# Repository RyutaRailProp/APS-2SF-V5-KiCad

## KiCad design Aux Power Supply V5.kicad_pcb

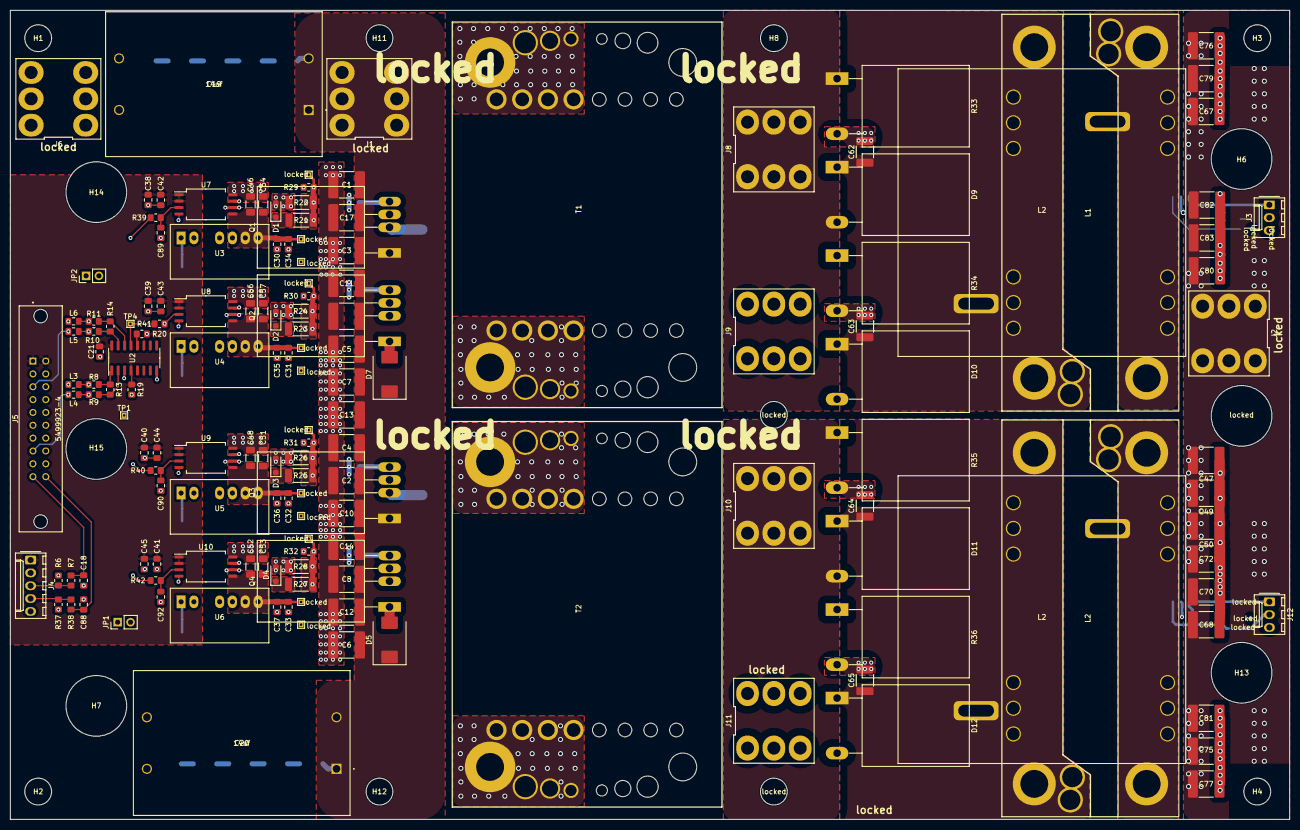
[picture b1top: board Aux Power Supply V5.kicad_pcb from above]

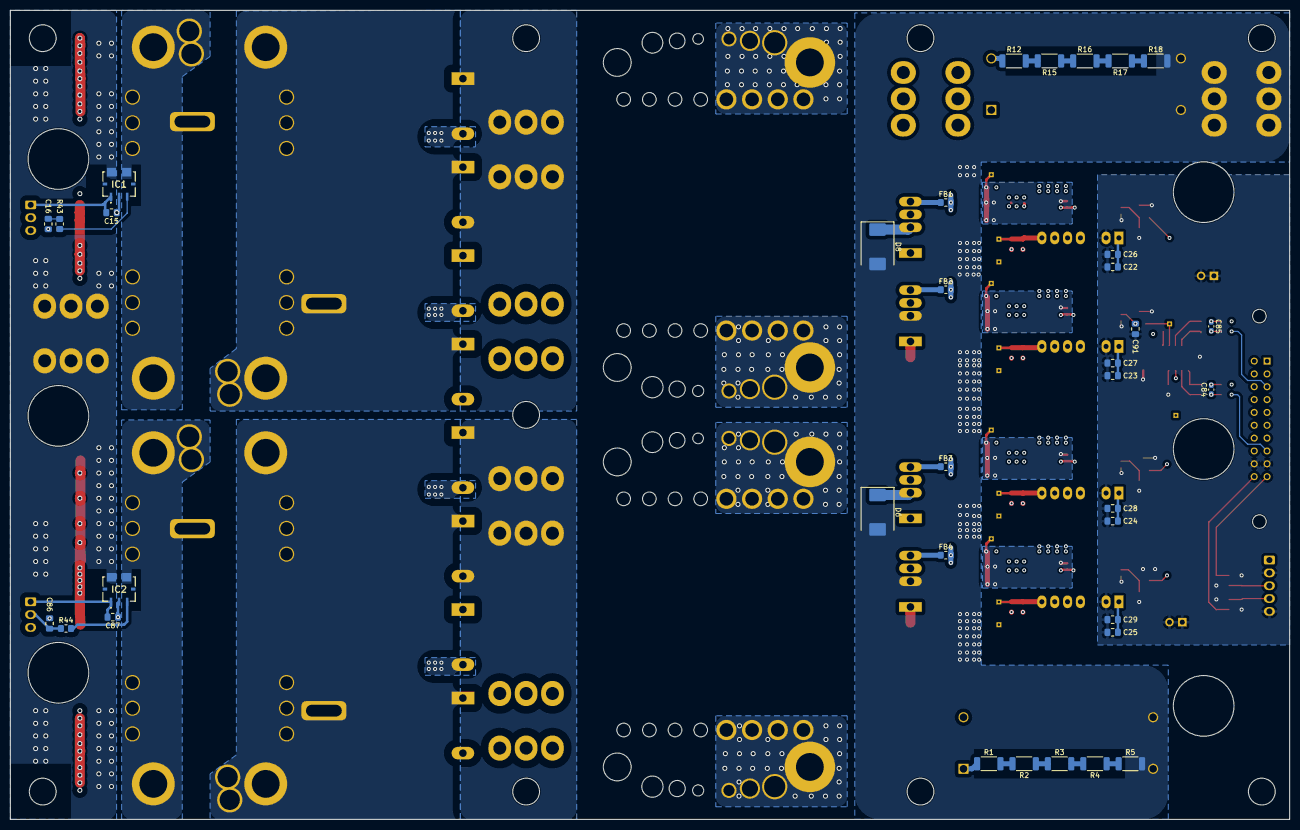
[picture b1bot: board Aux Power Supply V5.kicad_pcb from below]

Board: 4 copper layers, 253.0 x 160.0 mm, 208 parts (35 on the bottom side), 78 nets.

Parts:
C1, C2, C3, C4, C5, C6, C7, C8, C9, C10, C11, C12, C13, C14, C17: C; C_2220_5650Metric_Pad1.97x5.40mm_HandSolder
C15, C16, C21, C26, C27, C28, C29, C42, C43, C44, C45, C86, C87: 0.1uf; C_0805_2012Metric_Pad1.18x1.45mm_HandSolder
C18, C88: 3.9uf; C_0805_2012Metric_Pad1.18x1.45mm_HandSolder
C19, C20: 14uf; Film Cap, C4AxxBWxxxxx3J, 28 x 42 x 37
C22, C23, C24, C25, C34, C35, C36, C37: 4.7uf; C_0805_2012Metric_Pad1.18x1.45mm_HandSolder
C30, C31, C32, C33, C38, C39, C40, C41: 1uf; C_0805_2012Metric_Pad1.18x1.45mm_HandSolder
C46, C48, C51, C52, C53, C54, C56, C57: 0.1uf; C_1206_3216Metric_Pad1.33x1.80mm_HandSolder
C47, C49, C50, C67, C68, C70, C72, C75, C76, C77, C79, C80, C81, C82, C83: 22201C106KAT2A; C_2220_5650Metric_Pad1.97x5.40mm_HandSolder
C62, C63, C64, C65: 18121A472JAT2A; C_1812_4532Metric_Pad1.57x3.40mm_HandSolder
C84, C85: 56pF; C_0603_1608Metric_Pad1.08x0.95mm_HandSolder
C89, C90, C91, C92: 10uf; C_0805_2012Metric_Pad1.18x1.45mm_HandSolder
D1, D2, D3, D4: D_Small; D_SOD-123F
D5, D6, D7, D8: STTH212S; D_SMC
D9, D10, D11, D12: APT30S20BG; TO-247-2_Horizontal_TabDown_NoHole
FB1, FB2, FB3, FB4: 180ohm 100MHZ; R_0805_2012Metric_Pad1.20x1.40mm_HandSolder
H1, H2, H3, H4, H8, H11, H12: MountingHole; MountingHole_5.3mm_M5_DIN965
H6, H7, H13, H14, H15: MountingHole; MountingHole_12mm_M5_SpringClamp
IC1, IC2: ACS780LLRTR-050U-T; ACS780LLRTR050BT
J1, J2, J6, J8, J9, J10, J11: Screw_Terminal_01x01; 7808 Keystone M5 Terminal
J3, J12: I_Sense_R; Molex_KK-254_AE-6410-03A_1x03_P2.54mm_Vertical
J4: Conn_01x05; Molex_KK-254_AE-6410-05A_1x05_P2.54mm_Vertical
J5: 5499923-4; TE_5499923-4
JP1, JP2: Jumper; PinHeader_1x02_P2.54mm_Vertical
L1, L2#3: 26uH; ETD49 Core MB
L2, L2#2: 26uH; CWS-1HW-12203
L3, L4, L5, L6: 1uH; L_0805_2012Metric_Pad1.15x1.40mm_HandSolder
Q1, Q2, Q3, Q4: UJ4C075018K4S; TO-247-4_Horizontal_TabDown_NoHole
R1, R2, R3, R4, R5, R12, R15, R16, R17, R18: 100k; R_2010_5025Metric
R6, R13, R14, R19, R20, R29, R30, R31, R32, R37, R39, R40, R41, R42: 10k; R_0805_2012Metric_Pad1.20x1.40mm_HandSolder
R7, R38, R43, R44: 100R; R_0805_2012Metric_Pad1.20x1.40mm_HandSolder
R8, R9, R10, R11: 5k; R_0805_2012Metric_Pad1.20x1.40mm_HandSolder
R21, R23, R25, R27: 1; R_2010_5025Metric_Pad1.40x2.65mm_HandSolder
R22, R24, R26, R28: 5; R_2010_5025Metric_Pad1.40x2.65mm_HandSolder
R33, R34, R35, R36: R; TO-247-2_Horizontal_TabDown_NoHole
T1, T2: Transformer_1P_1S; E65 Core Main Board
TP1, TP4: IN+; TestPoint_THTPad_1.0x1.0mm_Drill0.5mm
TP5, TP6, TP7, TP8: +15H1; TestPoint_THTPad_1.0x1.0mm_Drill0.5mm
TP9, TP10, TP11, TP12: -5H1; TestPoint_THTPad_1.0x1.0mm_Drill0.5mm
TP13, TP14, TP15, TP16: PWM; TestPoint_THTPad_1.0x1.0mm_Drill0.5mm
U2: AM26LS33; SOIC-16_3.9x9.9mm_P1.27mm
U3, U4, U5, U6: AM2D-2418SZ; SIP-7 (pins 1, 2, 4,5, 6, 7)
U7, U8, U9, U10: STGAP2SICSC; SOIC-8_7.5x5.85mm_P1.27mm
locked: MountingHole; MountingHole_12mm_M5_SpringClamp
locked#2, locked#3: MountingHole; MountingHole_5.3mm_M5_DIN965

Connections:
1_HI: J5.5, L5.1
1_LO: J5.6, L6.1
2_HI: J5.16, L3.1
2_LO: J5.15, L4.1
+5V: C15.2, C21.1, C38.1, C39.1, C40.1, C41.1, C42.1, C43.1, C44.1, C45.1, C87.2, IC1.1 (VCC), IC2.1 (VCC), J3.1, J4.1, J5.1, J5.2, J12.1, R19.1, R20.2, U2.4 (EN), U2.16 (VDD), U7.1 (VCC), U7.2 (IN+), U8.1 (VCC), U8.2 (IN+), U9.1 (VCC), U9.2 (IN+), U10.1 (VCC), U10.2 (IN+)
+18V_BOT_T1: C31.1, C35.1, C56.1, C57.1, TP6.1, U4.7 (VOUT+), U8.5 (VCC2)
+18V_BOT_T2: C33.1, C37.1, C52.1, C53.1, TP8.1, U6.7 (VOUT+), U10.5 (VCC2)
+18V_TOP_T1: C30.1, C34.1, C46.1, C54.1, TP5.1, U3.7 (VOUT+), U7.5 (VCC2)
+18V_TOP_T2: C32.1, C36.1, C48.1, C51.1, TP7.1, U5.7 (VOUT+), U9.5 (VCC2)
+24V: C22.1, C23.1, C24.1, C25.1, C26.1, C27.1, C28.1, C29.1, J5.7, J5.8, U3.1 (VIN+), U4.1 (VIN+), U5.1 (VIN+), U6.1 (VIN+)
+72V_1: IC1.5 (IP+), L1.2, L2#2.2
+72V_2: IC2.5 (IP+), L2.2, L2#3.2
+72V_OUT: C47.2, C49.2, C50.2, C67.2, C68.2, C70.2, C72.2, C75.2, C76.2, C77.2, C79.2, C80.2, C81.2, C82.2, C83.2, IC1.6 (IP-), IC2.6 (IP-), J2.1
CLAMP_BOT_T1: FB2.2, R23.1, R24.1, R30.2, TP14.1, U8.7 (CLAMP)
CLAMP_BOT_T2: FB4.2, R27.1, R28.1, R32.2, TP16.1, U10.7 (CLAMP)
CLAMP_TOP_T1: FB1.2, R21.1, R22.1, R29.2, TP13.1, U7.7 (CLAMP)
CLAMP_TOP_T2: FB3.2, R25.1, R26.1, R31.2, TP15.1, U9.7 (CLAMP)
Ch1: R39.2, R41.2, TP4.1, U2.13 (Out4)
Ch2: R40.2, R42.2, TP1.1, U2.3 (Out1)
DC_IN: C1.1, C2.1, C3.1, C4.1, C5.1, C6.1, C7.1, C8.1, C9.1, C10.1, C11.1, C12.1, C13.1, C14.1, C17.1, C19.1, C20.1, D5.1 (K), D7.1 (K), J1.1, Q1.1 (D), Q3.1 (D), R1.1, R12.1
GATE_BOT_T1: D2.2 (A), R24.2, U8.6 (OUT)
GATE_BOT_T2: D4.2 (A), R28.2, U10.6 (OUT)
GATE_TOP_T1: D1.2 (A), R22.2, U7.6 (OUT)
GATE_TOP_T2: D3.2 (A), R26.2, U9.6 (OUT)
GND: C15.1, C16.2, C18.2, C21.2, C22.2, C23.2, C24.2, C25.2, C26.2, C27.2, C28.2, C29.2, C38.2, C39.2, C40.2, C41.2, C42.2, C43.2, C44.2, C45.2, C86.2, C87.1, C88.2, C89.1, C90.1, C91.1, C92.1, IC1.2 (GND), IC2.2 (GND), J3.3, J4.2, J4.5, J5.17, J5.18, J12.3, JP1.1, JP1.2, JP2.1, JP2.2, R6.1, R19.2, R37.1, U2.8 (GND), U3.2 (VIN-), U4.2 (VIN-), U5.2 (VIN-), U6.2 (VIN-), U7.4 (GND1), U8.4 (GND1), U9.4 (GND1), U10.4 (GND1)
GNDPWR: C1.2, C2.2, C3.2, C4.2, C5.2, C6.2, C7.2, C8.2, C9.2, C10.2, C11.2, C12.2, C13.2, C14.2, C17.2, C19.2, C20.2, D6.2 (A), D8.2 (A), J6.1, Q2.2 (S), Q4.2 (S), R5.2, R18.2
H1: R10.1, R14.2, U2.15 (B4)
H2: R8.1, R13.2, U2.1 (B1)
I_Sense_1: C18.1, J5.19, R7.2
I_Sense_2: C88.1, J5.20, R38.2
KELV_BOT_T1: C31.2, C35.2, C56.2, C57.2, Q2.3 (DS), R30.1, TP10.1, U4.5 (VOUT-), U8.8 (VEE)
KELV_BOT_T2: C33.2, C37.2, C52.2, C53.2, Q4.3 (DS), R32.1, TP12.1, U6.5 (VOUT-), U10.8 (VEE)
KELV_TOP_T1: C30.2, C34.2, C46.2, C54.2, Q1.3 (DS), R29.1, TP9.1, U3.5 (VOUT-), U7.8 (VEE)
KELV_TOP_T2: C32.2, C36.2, C48.2, C51.2, Q3.3 (DS), R31.1, TP11.1, U5.5 (VOUT-), U9.8 (VEE)
L1: R11.2, R14.1, U2.14 (A4)
L2: R9.2, R13.1, U2.2 (A1)
unnamed: C62.2, R33.2
unnamed: C63.2, R34.2
unnamed: C64.2, R35.2
unnamed: C65.2, R36.2
unnamed: C84.1, L4.2, R9.1
unnamed: C84.2, L3.2, R8.2
unnamed: C85.1, L6.2, R11.1
unnamed: C85.2, L5.2, R10.2
unnamed: D1.1 (K), R21.2
unnamed: D2.1 (K), R23.2
unnamed: D3.1 (K), R25.2
unnamed: D4.1 (K), R27.2
unnamed: D5.2 (A), Q4.1 (D), T2.2 (AB)
unnamed: D6.1 (K), Q3.2 (S), T2.1 (AA)
unnamed: D7.2 (A), Q2.1 (D), T1.2 (AB)
unnamed: D8.1 (K), Q1.2 (S), T1.1 (AA)
unnamed: C62.1, C63.1, D9.1 (K), D10.1 (K), L1.1, L2#2.1
unnamed: C64.1, C65.1, D11.1 (K), D12.1 (K), L2.1, L2#3.1
unnamed: IC1.3 (VOUT), R43.2
unnamed: IC2.3 (VOUT), R44.2
unnamed: FB1.1, Q1.4 (G)
unnamed: FB2.1, Q2.4 (G)
unnamed: FB3.1, Q3.4 (G)
unnamed: FB4.1, Q4.4 (G)
unnamed: R1.2, R2.2
unnamed: R2.1, R3.1
unnamed: R3.2, R4.2
unnamed: R4.1, R5.1
unnamed: R12.2, R15.2
unnamed: R15.1, R16.1
unnamed: R16.2, R17.2
unnamed: R17.1, R18.1
unnamed: R20.1, U2.12 (~EN)
unnamed: C89.2, R39.1, U7.3 (IN-)
unnamed: C91.2, R41.1, U8.3 (IN-)
unnamed: C90.2, R40.1, U9.3 (IN-)
unnamed: C92.2, R42.1, U10.3 (IN-)
OUTPUT_GND: C47.1, C49.1, C50.1, C67.1, C68.1, C70.1, C72.1, C75.1, C76.1, C77.1, C79.1, C80.1, C81.1, C82.1, C83.1, D10.2 (A), D12.2 (A), J9.1, J11.1, R34.1, R36.1
SO1: C16.1, J3.2, J4.3, R6.2, R7.1, R43.1
SO2: C86.1, J4.4, J12.2, R37.2, R38.1, R44.1
T1_OUT: D9.2 (A), J8.1, R33.1
T2_OUT: D11.2 (A), J10.1, R35.1

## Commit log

2023-12-22 changed bypass cap values to correct vals
2023-12-22 updated documentation
2023-12-22 locked PCB editor

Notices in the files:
parts and their libraries:
Copyright 2021 Accelerated Designs. All rights reserved.
